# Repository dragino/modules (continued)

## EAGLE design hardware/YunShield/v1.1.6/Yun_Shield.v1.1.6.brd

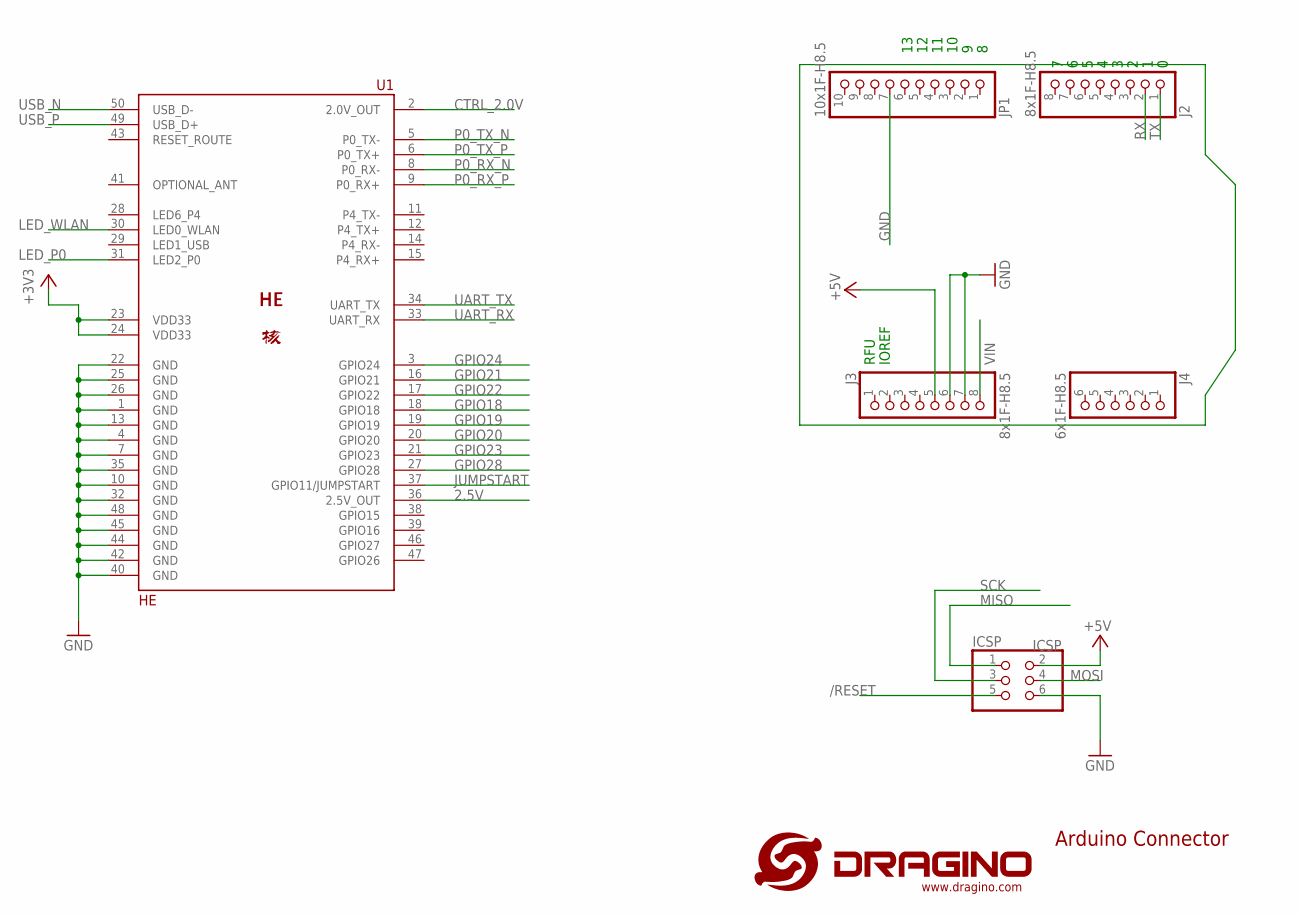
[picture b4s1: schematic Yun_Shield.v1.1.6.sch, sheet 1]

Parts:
ICSP: ICSP; 2X03
J2, J3: 8x1F-H8.5; 1X08
J4: 6x1F-H8.5; 1X06
JP1: 10x1F-H8.5; 1X10
U1: HE; HE50
U$1: LOGO-NEW; LOGO-SILK-NEW

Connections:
2.5V: U1.36 (2.5V_OUT)
5V: ICSP.2
+3V3: U1.23 (VDD33), U1.24 (VDD33); also elsewhere on the board
+5V: J3.5; also elsewhere on the board
/RESET: ICSP.5; also elsewhere on the board
CTRL_2.0V: U1.2 (2.0V_OUT); also elsewhere on the board
GND: ICSP.6, J3.6, J3.7, JP1.7, U1.1 (GND), U1.4 (GND), U1.7 (GND), U1.10 (GND), U1.13 (GND), U1.22 (GND), U1.25 (GND), U1.26 (GND), U1.32 (GND), U1.35 (GND), U1.40 (GND), U1.42 (GND), U1.44 (GND), U1.45 (GND), U1.48 (GND); also elsewhere on the board
GPIO18: U1.18 (GPIO18); also elsewhere on the board
GPIO19: U1.19 (GPIO19); also elsewhere on the board
GPIO20: U1.20 (GPIO20); also elsewhere on the board
GPIO21: U1.16 (GPIO21); also elsewhere on the board
GPIO22: U1.17 (GPIO22); also elsewhere on the board
GPIO23: U1.21 (GPIO23); also elsewhere on the board
GPIO24: U1.3 (GPIO24); also elsewhere on the board
GPIO28: U1.27 (GPIO28); also elsewhere on the board
JUMPSTART: U1.37 (GPIO11/JUMPSTART); also elsewhere on the board
LED_P0: U1.31 (LED2_P0); also elsewhere on the board
LED_WLAN: U1.30 (LED0_WLAN); also elsewhere on the board
MISO: ICSP.1; also elsewhere on the board
MOSI: ICSP.4; also elsewhere on the board
OPTIONAL_ANT: U1.41 (OPTIONAL_ANT)
P0_RX_N: U1.8 (P0_RX-); also elsewhere on the board
P0_RX_P: U1.9 (P0_RX+); also elsewhere on the board
P0_TX_N: U1.5 (P0_TX-); also elsewhere on the board
P0_TX_P: U1.6 (P0_TX+); also elsewhere on the board
RX: J2.2; also elsewhere on the board
SCK: ICSP.3; also elsewhere on the board
TX: J2.1; also elsewhere on the board
UART_RX: U1.33 (UART_RX); also elsewhere on the board
UART_TX: U1.34 (UART_TX); also elsewhere on the board
USB_N: U1.50 (USB_D-); also elsewhere on the board
USB_P: U1.49 (USB_D+); also elsewhere on the board
VIN: J3.8; also elsewhere on the board

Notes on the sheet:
IOREF
RFU
Arduino Connector

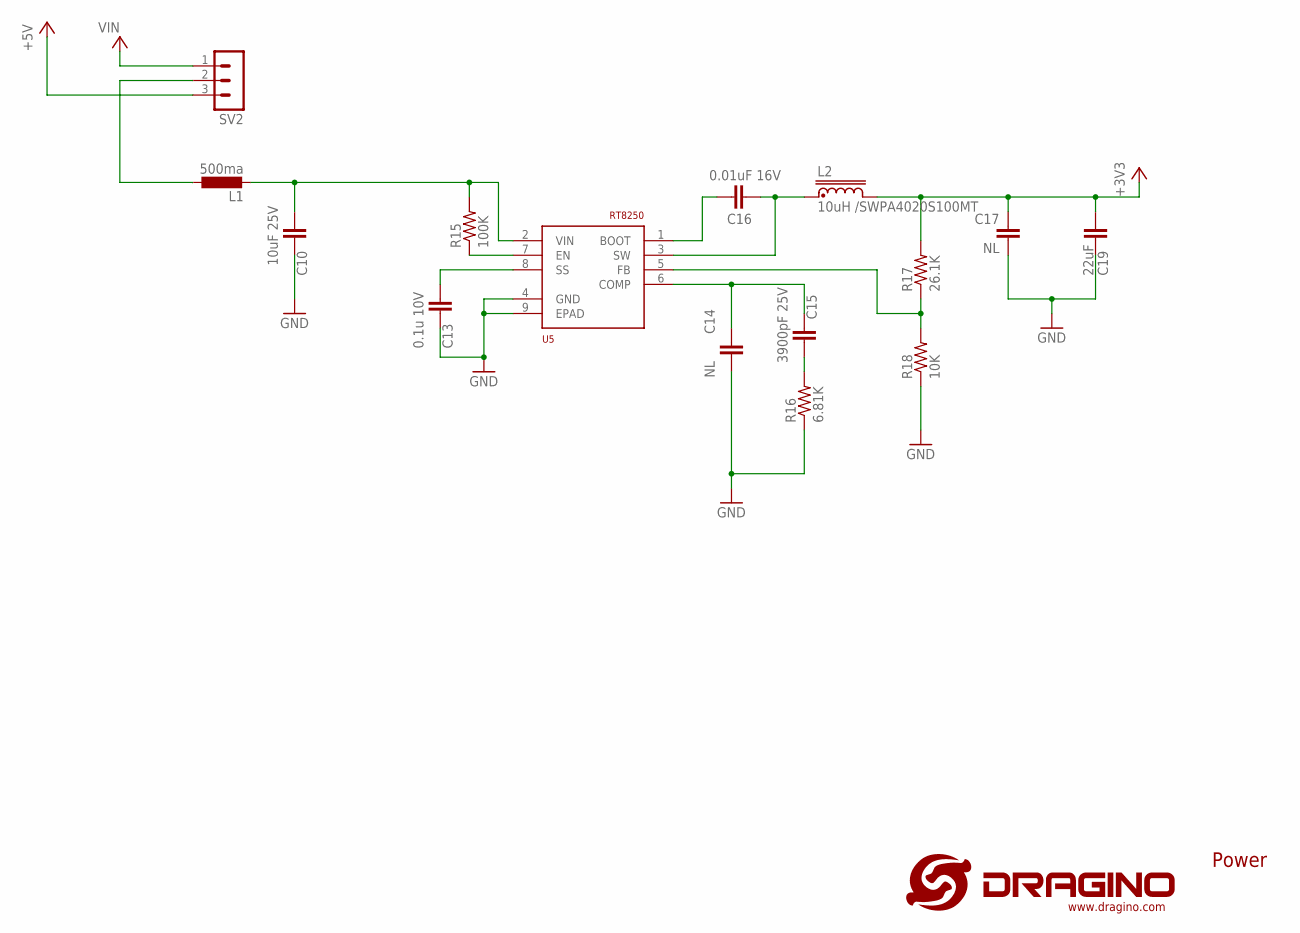
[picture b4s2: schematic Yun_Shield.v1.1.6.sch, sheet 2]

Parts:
C10: 10uF 25V; C1206
C13: 0.1u 10V; C0402
C14, C17: NL; C0402
C15: 3900pF 25V; C0402
C16: 0.01uF 16V; C0402
C19: 22uF; C1210
L1: 500ma; L1812
L2: 10uH /SWPA4020S100MT; SWPA4020S
R15: 100K; R0402
R16: 6.81K; R0402
R17: 26.1K; R0402
R18: 10K; R0402
SV2: MA03-1
U5: RT8250; RT8250-SOP8

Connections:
+3V3: C17.1, C19.1, L2.P$2 (4), R17.2; also elsewhere on the board
+5V: SV2.3; also elsewhere on the board
GND: C10.1, C13.2, C14.2, C17.2, C19.2, R16.1, R18.1, U5.4 (GND), U5.9 (EPAD); also elsewhere on the board
unnamed: C10.2, L1.2, R15.2, U5.2 (VIN)
unnamed: R15.1, U5.7 (EN)
unnamed: R17.1, R18.2, U5.5 (FB)
unnamed: C13.1, U5.8 (SS)
unnamed: C14.1, C15.1, U5.6 (COMP)
unnamed: C15.2, R16.2
unnamed: C16.1, U5.1 (BOOT)
unnamed: C16.2, L2.P$1 (1), U5.3 (SW)
VCC: L1.1, SV2.2
VIN: SV2.1; also elsewhere on the board

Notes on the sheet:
Power

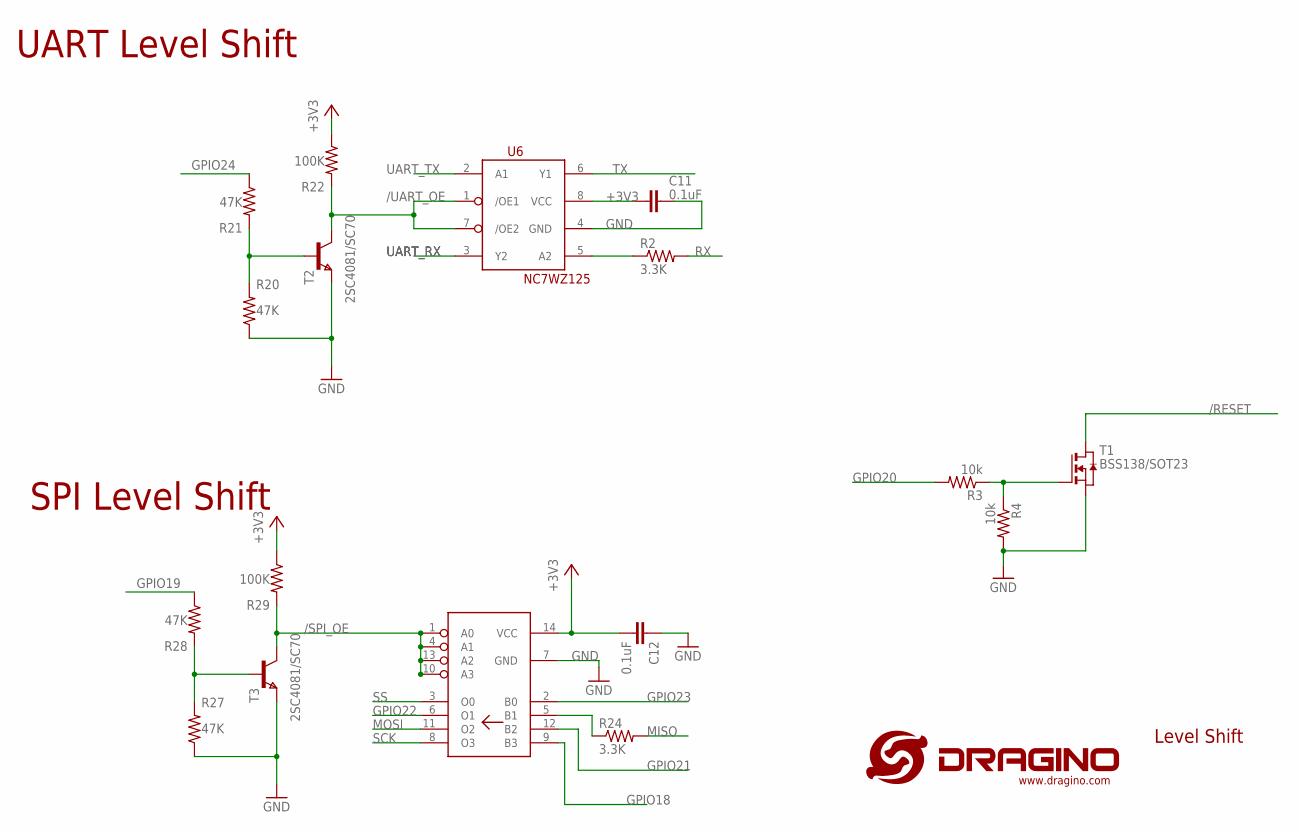
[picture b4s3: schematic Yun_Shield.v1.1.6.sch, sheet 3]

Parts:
C11, C12: 0.1uF; C0402
R2, R24: 3.3K; R0402
R3, R4: 10k; R0402
R20, R21, R27, R28: 47K; R0402
R22, R29: 100K; R0402
T1: BSS138/SOT23; SOT-23
T2, T3: 2SC4081/SC70; SOT323
U6: NC7WZ125; US8
U7: 74VHC125

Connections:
+3V3: C11.2, C12.2, R22.1, R29.1, U6.8 (VCC), U7.14 (VCC); also elsewhere on the board
/RESET: T1.1 (D); also elsewhere on the board
/SPI_OE: R29.2, T3.1 (C), U7.1 (A0), U7.4 (A1), U7.10 (A3), U7.13 (A2)
/UART_OE: R22.2, T2.1 (C), U6.1 (/OE1), U6.7 (/OE2)
GND: C11.1, C12.1, R4.2, R20.1, R27.1, T1.2 (S), T2.3 (E), T3.3 (E), U6.4 (GND), U7.7 (GND); also elsewhere on the board
GPIO18: U7.9 (B3); also elsewhere on the board
GPIO19: R28.1; also elsewhere on the board
GPIO20: R3.2; also elsewhere on the board
GPIO21: U7.12 (B2); also elsewhere on the board
GPIO22: U7.6 (O1); also elsewhere on the board
GPIO23: U7.2 (B0); also elsewhere on the board
GPIO24: R21.1; also elsewhere on the board
MISO: R24.2; also elsewhere on the board
MOSI: U7.11 (O2); also elsewhere on the board
unnamed: R3.1, R4.1, T1.3 (G)
unnamed: R20.2, R21.2, T2.2 (B)
unnamed: R27.2, R28.2, T3.2 (B)
unnamed: R2.1, U6.5 (A2)
unnamed: R24.1, U7.5 (B1)
RX: R2.2; also elsewhere on the board
SCK: U7.8 (O3); also elsewhere on the board
SS: U7.3 (O0)
TX: U6.6 (Y1); also elsewhere on the board
UART_RX: U6.3 (Y2); also elsewhere on the board
UART_TX: U6.2 (A1); also elsewhere on the board

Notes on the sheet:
Level Shift
UART Level Shift
SPI Level Shift

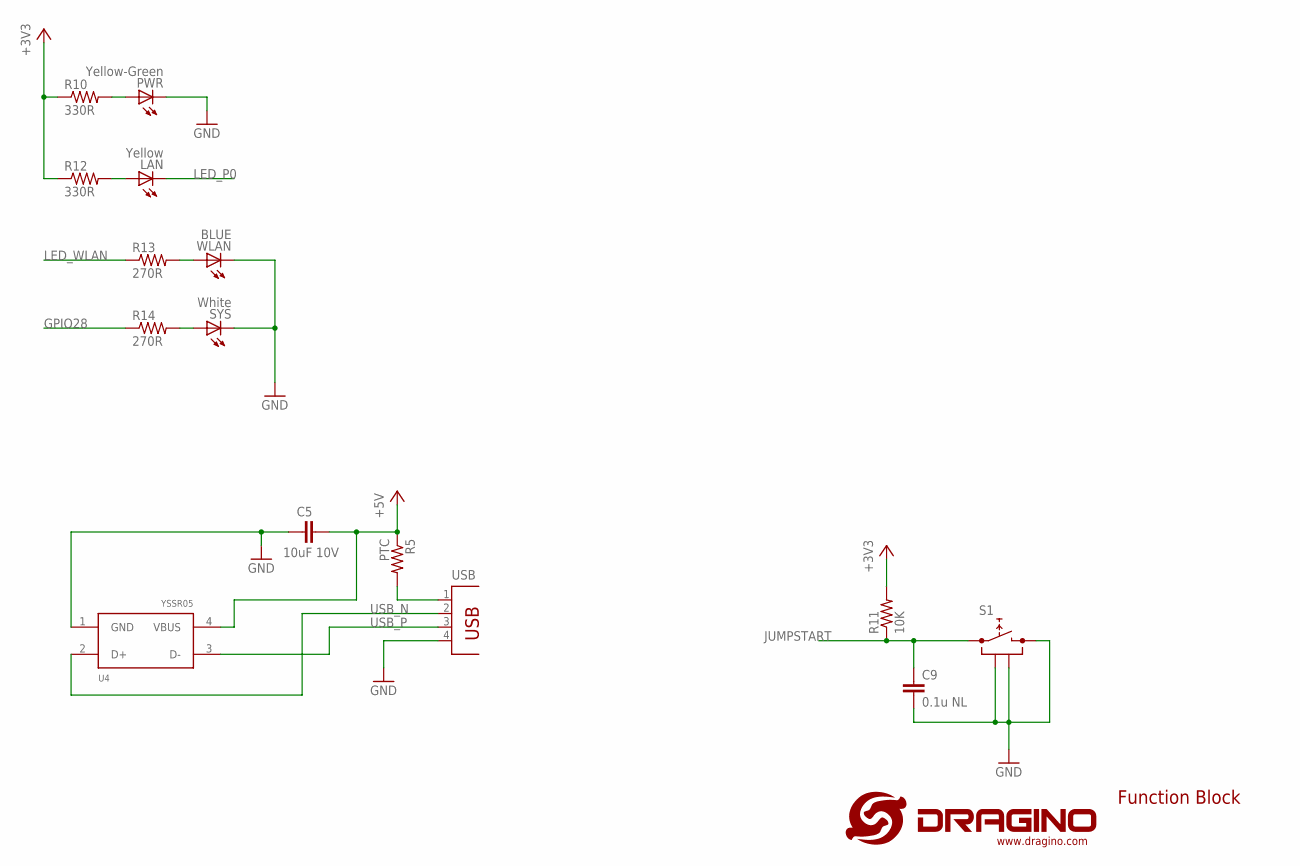
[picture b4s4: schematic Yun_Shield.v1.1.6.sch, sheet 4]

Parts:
C5: 10uF 10V; C0805
C9: 0.1u NL; C0402
LAN: Yellow; CHIP-LED0603
PWR: Yellow-Green; CHIP-LED0603
R5: PTC; R0805
R10, R12: 330R; R0402
R11: 10K; R0402
R13, R14: 270R; R0402
S1: PUSH_SWITCH; SWITCH_6X6X5
SYS: White; CHIP-LED0603
U4: YSSR05; SOT143
USB: PN87520
WLAN: BLUE; CHIP-LED0603

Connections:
+3V3: R10.1, R11.2, R12.1; also elsewhere on the board
+5V: C5.1, R5.1, U4.4 (VBUS); also elsewhere on the board
GND: C5.2, C9.2, PWR.C, S1.2, S1.3, S1.4, SYS.C, U4.1 (GND), USB.4, WLAN.C; also elsewhere on the board
GPIO28: R14.1; also elsewhere on the board
JUMPSTART: C9.1, R11.1, S1.1; also elsewhere on the board
LED_P0: LAN.C; also elsewhere on the board
LED_WLAN: R13.1; also elsewhere on the board
unnamed: R5.2, USB.1
unnamed: PWR.A, R10.2
unnamed: LAN.A, R12.2
unnamed: R13.2, WLAN.A
unnamed: R14.2, SYS.A
USB_N: U4.2 (D+), USB.2; also elsewhere on the board
USB_P: U4.3 (D-), USB.3; also elsewhere on the board

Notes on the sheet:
Function Block

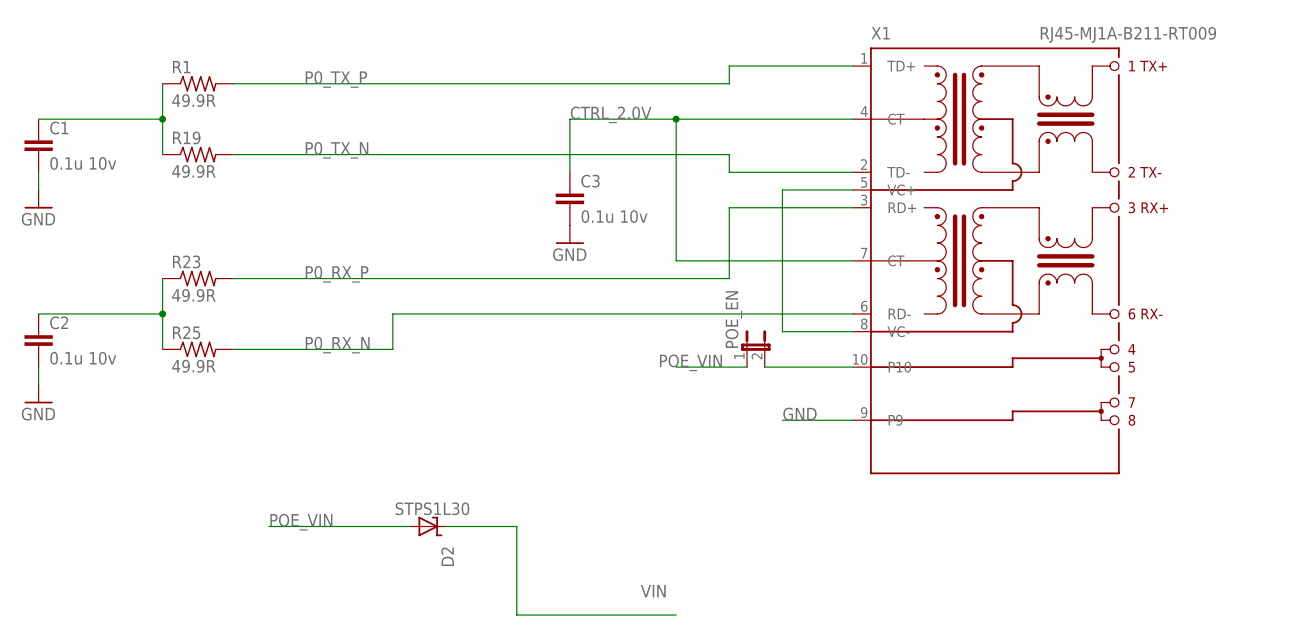
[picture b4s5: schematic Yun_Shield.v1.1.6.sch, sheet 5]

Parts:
C1, C2, C3: 0.1u 10v; C0402
D2: STPS1L30; DO214AC
POE_EN: JP1E; JP1
R1, R19, R23, R25: 49.9R; R0402
X1: RJ45-MJ1A-B211-RT009; MJ1A-B211-RT009

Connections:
CTRL_2.0V: C3.1, X1.4 (CT), X1.7 (CT); also elsewhere on the board
GND: C1.2, C2.2, C3.2, X1.9; also elsewhere on the board
unnamed: POE_EN.2, X1.10
unnamed: X1.5 (VC+), X1.8 (VC-)
unnamed: C1.1, R1.1, R19.1
unnamed: C2.1, R23.1, R25.1
P0_RX_N: R25.2, X1.6 (RD-); also elsewhere on the board
P0_RX_P: R23.2, X1.3 (RD+); also elsewhere on the board
P0_TX_N: R19.2, X1.2 (TD-); also elsewhere on the board
P0_TX_P: R1.2, X1.1 (TD+); also elsewhere on the board
POE_VIN: D2.A, POE_EN.1
VIN: D2.C; also elsewhere on the board

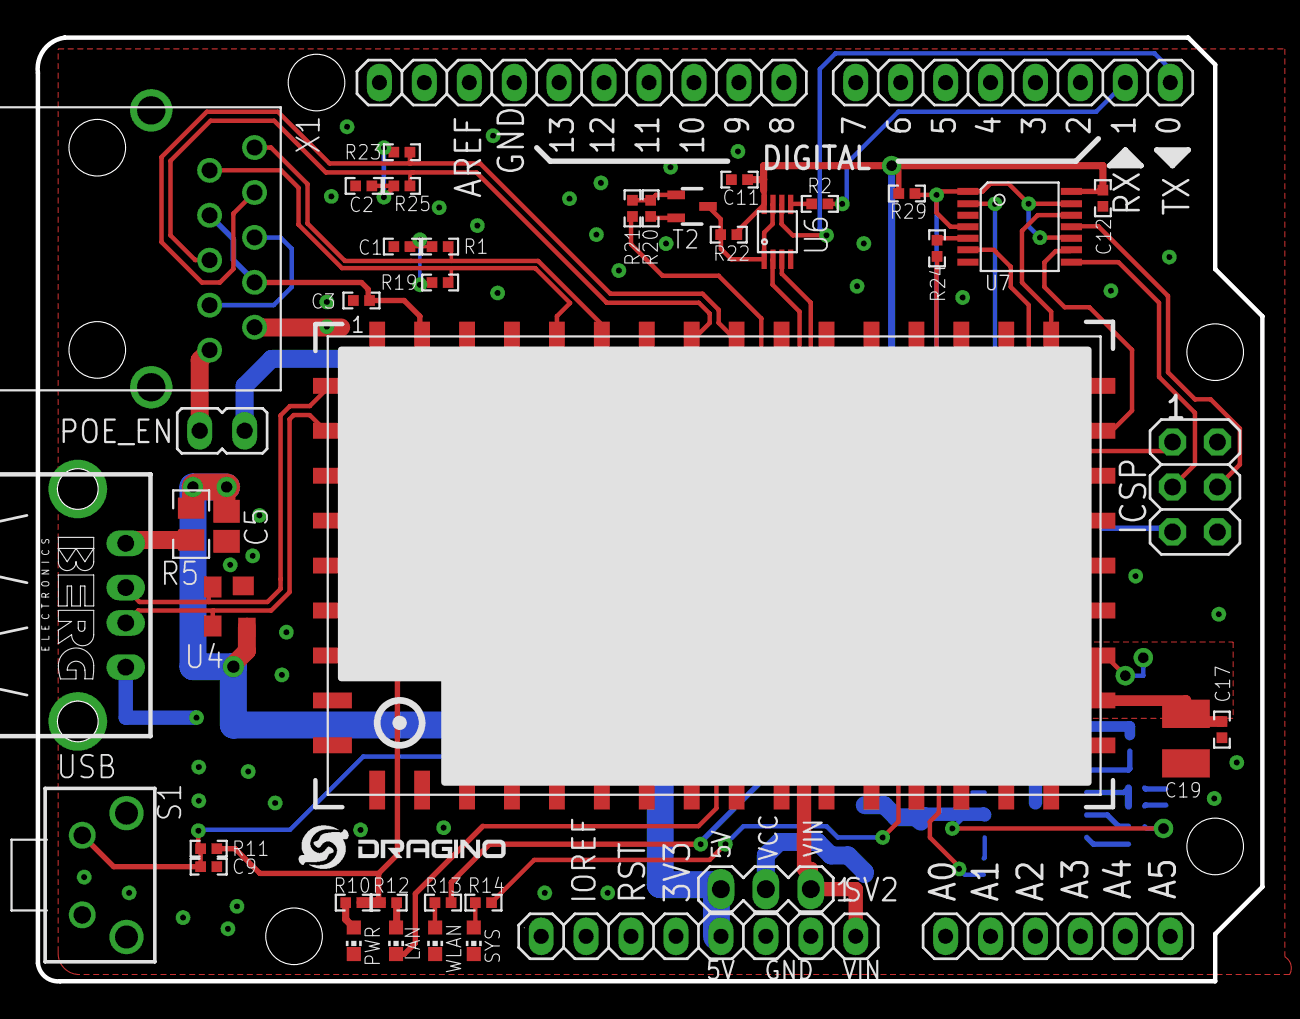
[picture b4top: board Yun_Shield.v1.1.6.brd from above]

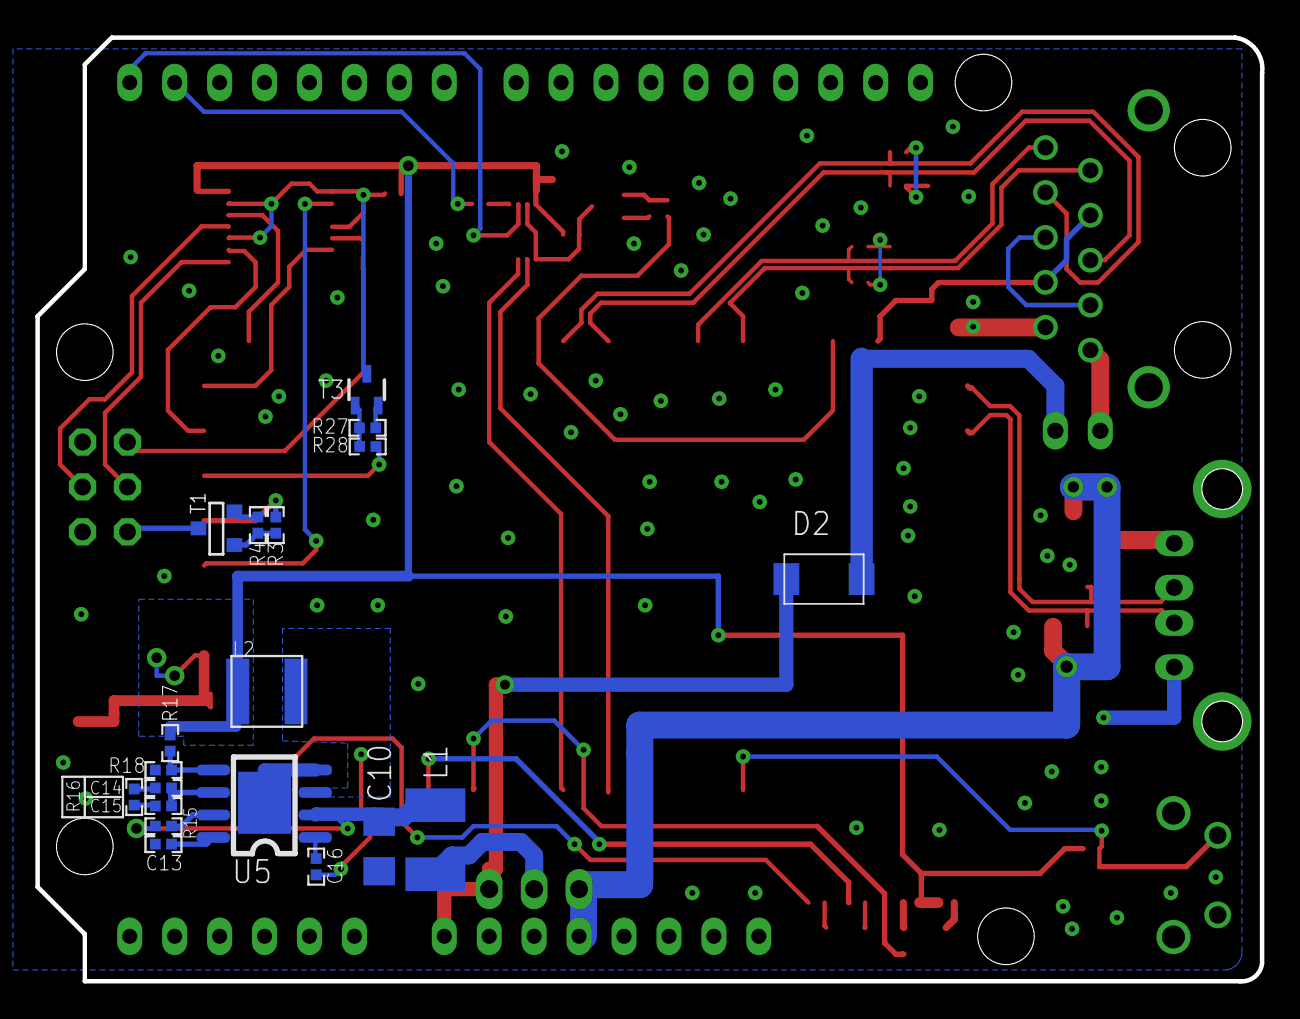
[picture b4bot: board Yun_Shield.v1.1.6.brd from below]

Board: 2 copper layers, 69.2 x 53.3 mm, 64 parts (19 on the bottom side), 56 nets.

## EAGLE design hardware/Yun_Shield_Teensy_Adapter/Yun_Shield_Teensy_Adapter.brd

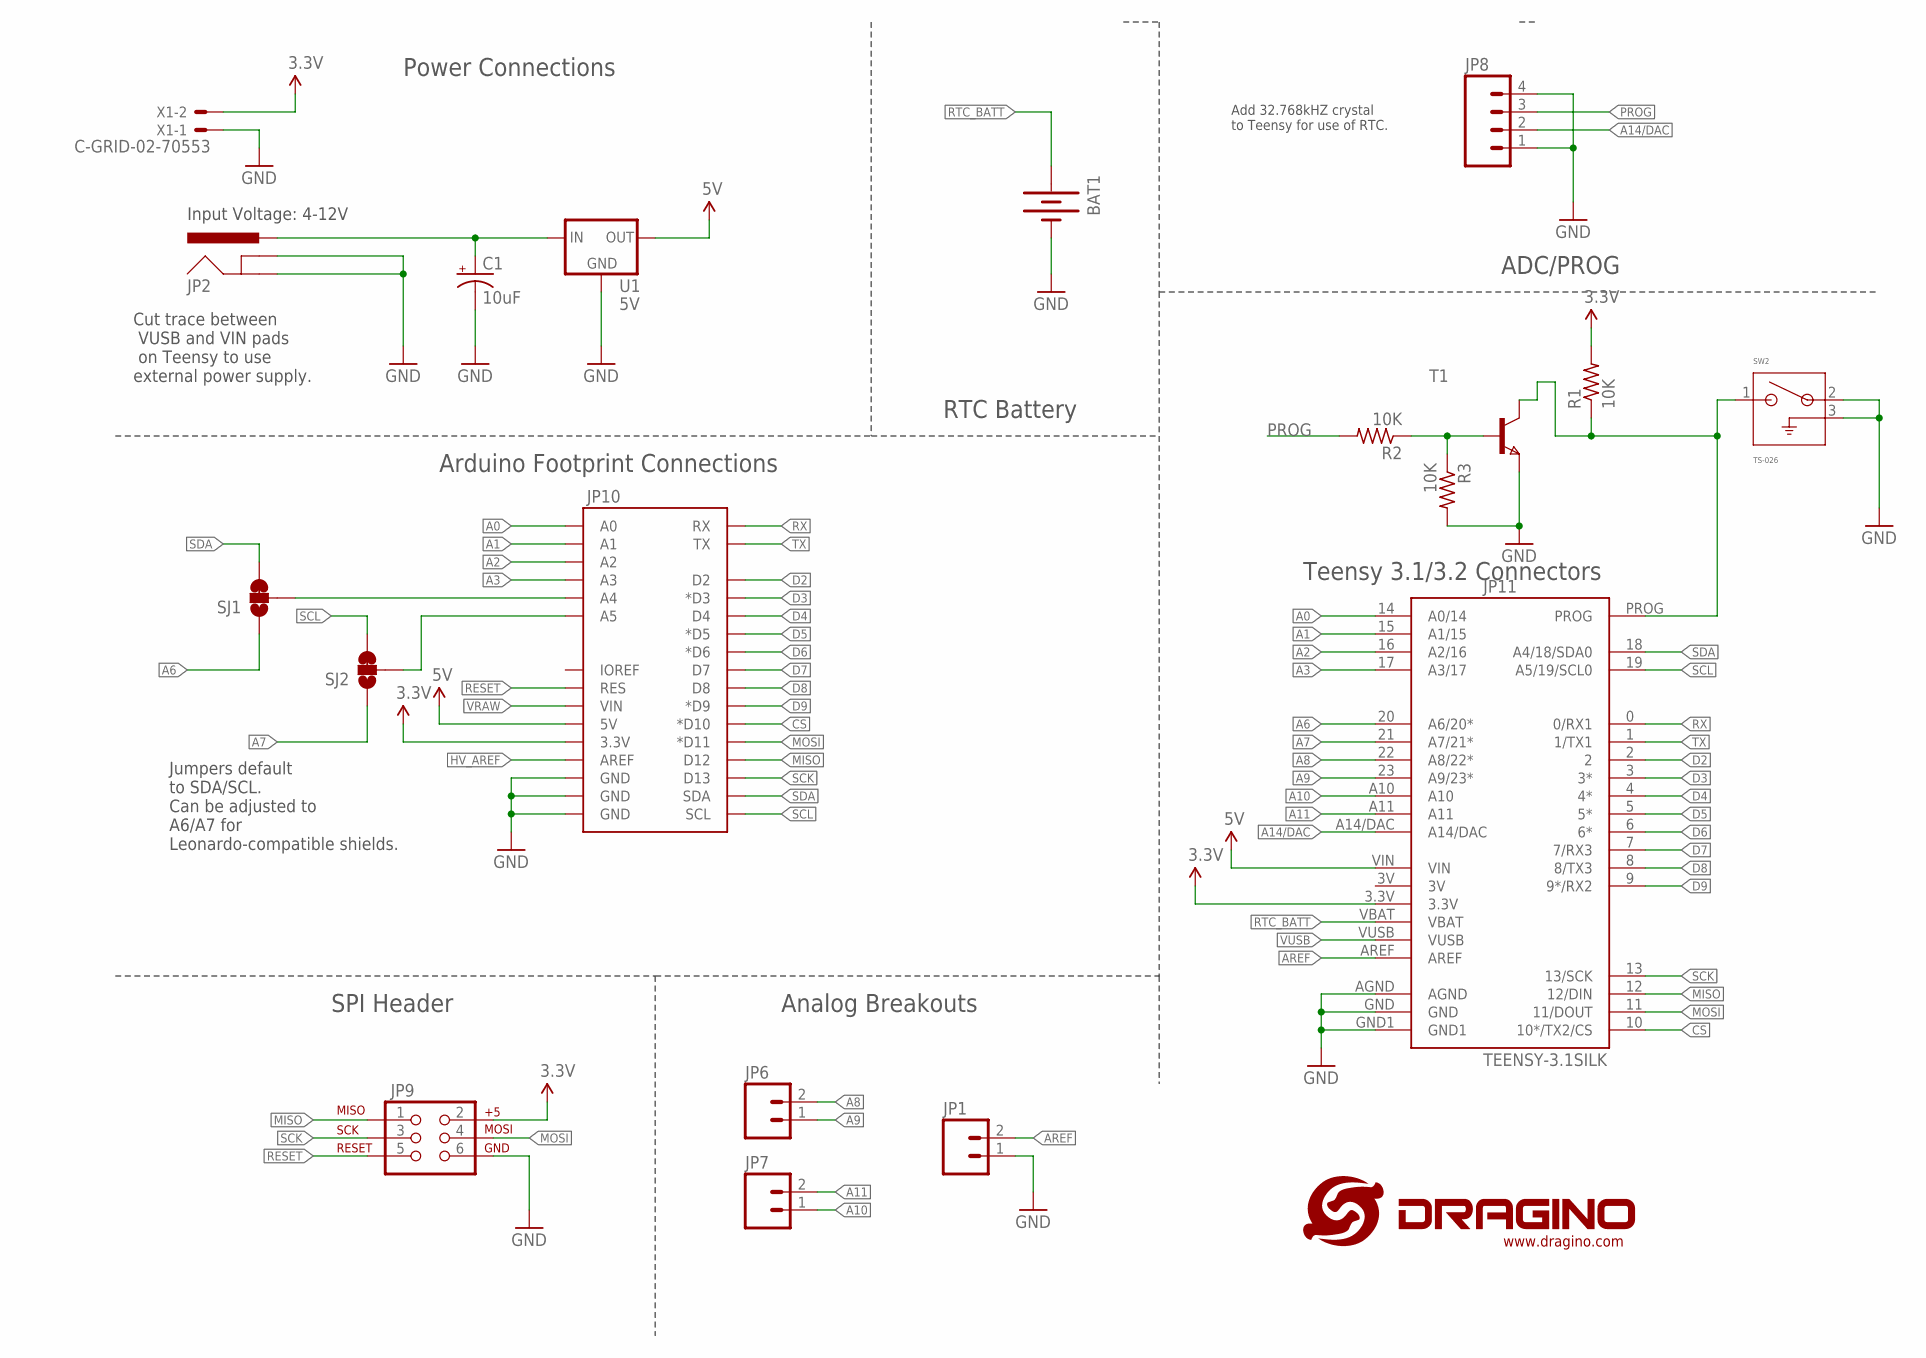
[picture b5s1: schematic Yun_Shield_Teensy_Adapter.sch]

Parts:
BAT1: BATTERY12PTH; BATTCON_12MM_PTH
C1: 10uF; CPOL-RADIAL-10UF-25V
JP1, JP6, JP7: M02PTH; 1X02
JP2: POWER_JACKPTH_LOCK; POWER_JACK_PTH_LOCK
JP8: M04PTH; 1X04
JP9: AVR_SPI_PRG_6PTH; 2X3
JP10: ARDUINO_R3_SHIELDUNO_R3_SHIELD_HOLES; UNO_R3_SHIELD_HOLES
JP11: TEENSY-3.1SILK; TEENSY-3.1
R1, R2, R3: 10K; 0204/5
SJ1, SJ2: JUMPER-PAD-3-2OF3_NC_BY_TRACE_SMALL; PAD-JUMPER-3-2OF3_NC_BY_TRACE_YES_SILK_FULL_BOX
SW2: TS-026
T1: NPN-E3L; E3LINE
U1: 5V; TO-220-ALT
U$1: LOGO-NEW; LOGO-SILK-NEW
X1: C-GRID-02-70553; 70553-02

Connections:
3.3V: JP9.2, JP10.3.3V, JP11.3.3V, R1.2, X1.2
5V: JP10.5V, JP11.VIN, U1.OUT
A0: JP10.A0, JP11.14 (A0/14)
A1: JP10.A1, JP11.15 (A1/15)
A2: JP10.A2, JP11.16 (A2/16)
A3: JP10.A3, JP11.17 (A3/17)
A4: JP10.A4, SJ1.2
A5: JP10.A5, SJ2.2
A6: JP11.20 (A6/20*), SJ1.1
A7: JP11.21 (A7/21*), SJ2.1
A8: JP6.2, JP11.22 (A8/22*)
A9: JP6.1, JP11.23 (A9/23*)
A10: JP7.1, JP11.A10
A11: JP7.2, JP11.A11
A14/DAC: JP8.2, JP11.A14/DAC
AREF: JP1.2, JP11.AREF
CS: JP10.D10 (*D10), JP11.10 (10*/TX2/CS)
D2: JP10.D2, JP11.2
D3: JP10.D3 (*D3), JP11.3 (3*)
D4: JP10.D4, JP11.4 (4*)
D5: JP10.D5 (*D5), JP11.5 (5*)
D6: JP10.D6 (*D6), JP11.6 (6*)
D7: JP10.D7, JP11.7 (7/RX3)
D8: JP10.D8, JP11.8 (8/TX3)
D9: JP10.D9 (*D9), JP11.9 (9*/RX2)
GND: BAT1.GND (-), C1.2 (-), JP1.1, JP2.GND, JP2.GNDBREAK, JP8.1, JP8.4, JP9.6, JP10.GND@0 (GND), JP10.GND@1 (GND), JP10.GND@2 (GND), JP11.AGND, JP11.GND, JP11.GND1, R3.2, SW2.2, SW2.3, T1.3 (E), U1.GND, X1.1
HV_AREF: JP10.AREF
MISO: JP9.1, JP10.D12, JP11.12 (12/DIN)
MOSI: JP9.4, JP10.D11 (*D11), JP11.11 (11/DOUT)
unnamed: JP11.PROG, R1.1, SW2.1, T1.1 (C)
unnamed: R2.1, R3.1, T1.2 (B)
PROG: JP8.3, R2.2
RESET: JP9.5, JP10.RES
RTC_BATT: BAT1.VCC@1 (+), JP11.VBAT
RX: JP10.RX, JP11.0 (0/RX1)
SCK: JP9.3, JP10.D13, JP11.13 (13/SCK)
SCL: JP10.SCL, JP11.19 (A5/19/SCL0), SJ2.3
SDA: JP10.SDA, JP11.18 (A4/18/SDA0), SJ1.3
TX: JP10.TX, JP11.1 (1/TX1)
VRAW: C1.1 (+), JP2.PWR, JP10.VIN, U1.IN
VUSB: JP11.VUSB

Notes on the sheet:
Input Voltage: 4-12V
Add 32.768kHZ crystal to Teensy for use of RTC.
Cut trace between VUSB and VIN pads on Teensy to use external power supply.
Jumpers default to SDA/SCL. Can be adjusted to A6/A7 for Leonardo-compatible shields.
Power Connections
Arduino Footprint Connections
SPI Header
Analog Breakouts
Teensy 3.1/3.2 Connectors
ADC/PROG
RTC Battery

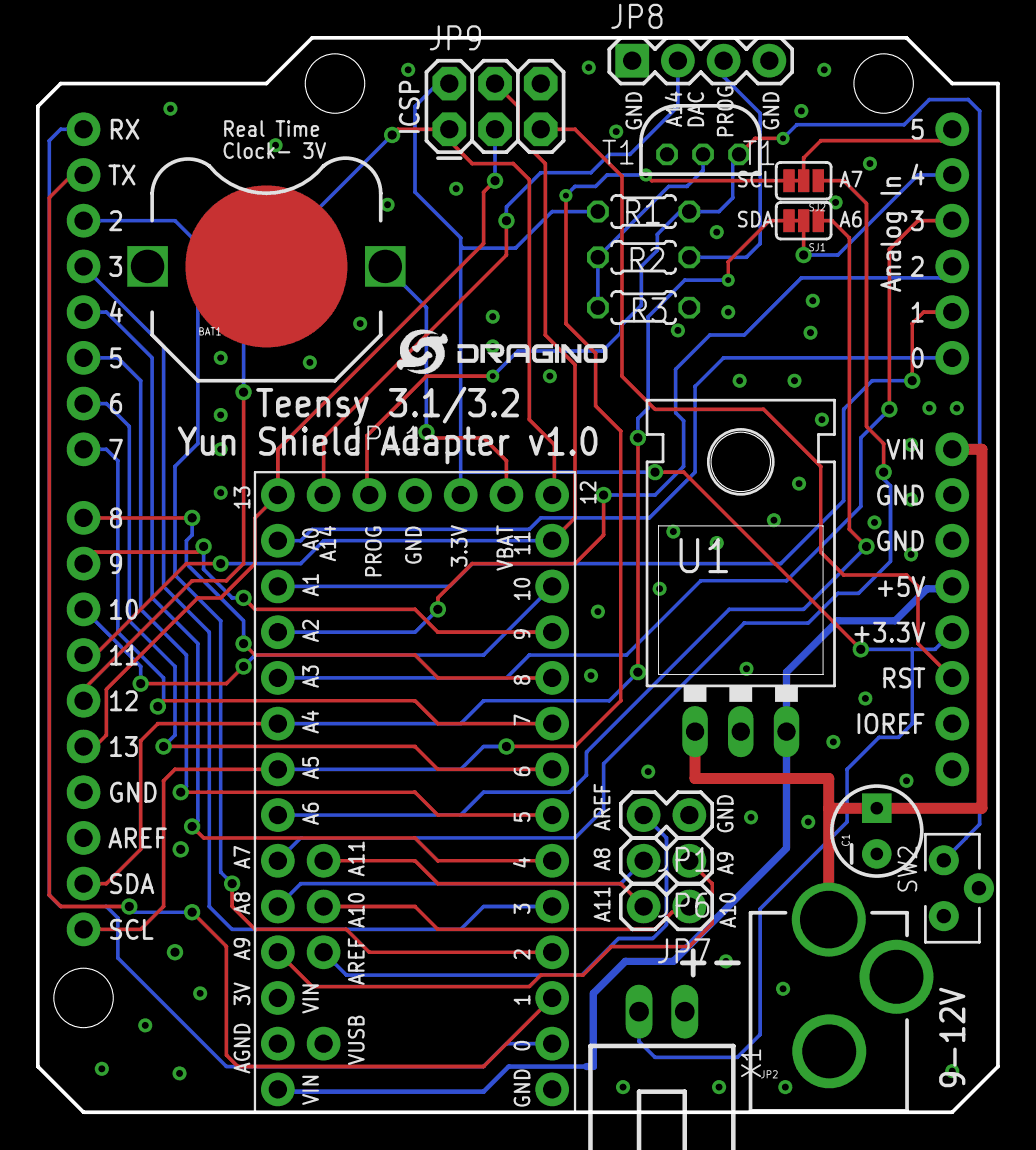
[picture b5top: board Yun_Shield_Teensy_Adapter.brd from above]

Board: 2 copper layers, 53.3 x 59.7 mm, 20 parts (0 on the bottom side), 39 nets.

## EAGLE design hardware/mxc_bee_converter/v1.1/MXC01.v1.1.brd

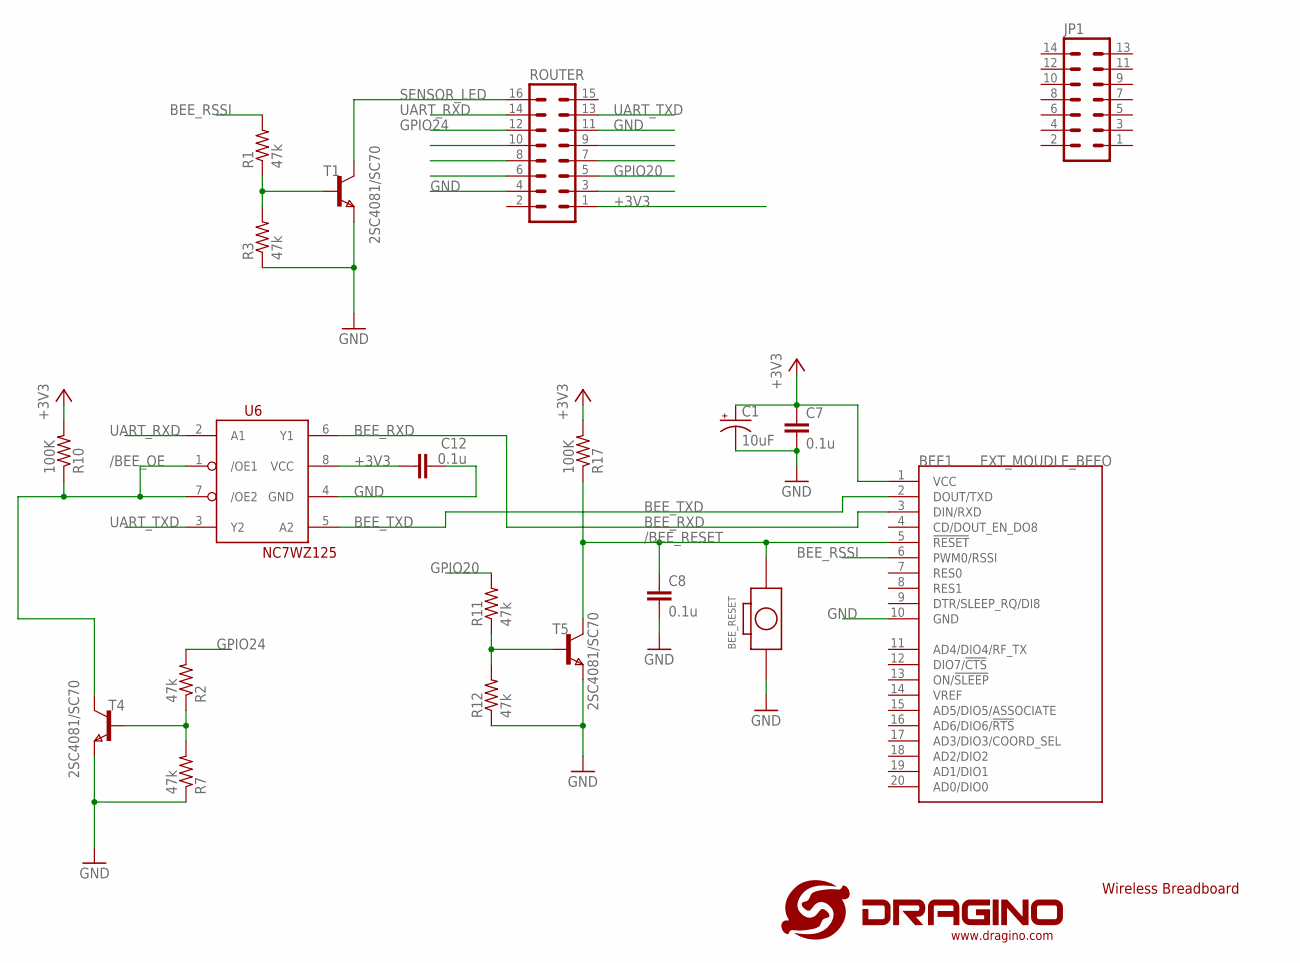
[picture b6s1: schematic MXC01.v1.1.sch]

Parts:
BEE1: EXT_MOUDLE_BEEO; EXT_MOUDLE_BEE
BEE_RESET: CPT_SMD_BOTTON_1_SMD; CPT_SMD_BOTTON_1
C1: 10uF; SMC_A
C7, C8, C12: 0.1u; C0402
JP1: MA07-2
R1, R2, R3, R7, R11, R12: 47k; R0402
R10, R17: 100K; R0402
ROUTER: MA08-2
T1, T4, T5: 2SC4081/SC70; SOT323
U6: NC7WZ125; US8
U$1: LOGO-NEW; LOGO-SILK-NEW

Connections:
+3V3: BEE1.1 (VCC), C1.+, C7.1, C12.1, R10.2, R17.2, ROUTER.1, U6.8 (VCC)
/BEE_OE: R10.1, T4.1 (C), U6.1 (/OE1), U6.7 (/OE2)
/BEE_RESET: BEE1.5 (!RESET), BEE_RESET.P$2 (2), C8.1, R17.1, T5.1 (C)
BEE_RSSI: BEE1.6 (PWM0/RSSI), R1.2
BEE_RXD: BEE1.3 (DIN/RXD), U6.6 (Y1)
BEE_TXD: BEE1.2 (DOUT/TXD), U6.5 (A2)
GND: BEE1.10 (GND), BEE_RESET.1, C1.-, C7.2, C8.2, C12.2, R3.1, R7.1, R12.1, ROUTER.4, ROUTER.11, T1.3 (E), T4.3 (E), T5.3 (E), U6.4 (GND)
GPIO20: R11.2, ROUTER.5
GPIO24: R2.2, ROUTER.12
unnamed: R1.1, R3.2, T1.2 (B)
unnamed: R2.1, R7.2, T4.2 (B)
unnamed: R11.1, R12.2, T5.2 (B)
SENSOR_LED: ROUTER.16, T1.1 (C)
UART_RXD: ROUTER.14, U6.2 (A1)
UART_TXD: ROUTER.13, U6.3 (Y2)

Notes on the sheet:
Wireless Breadboard

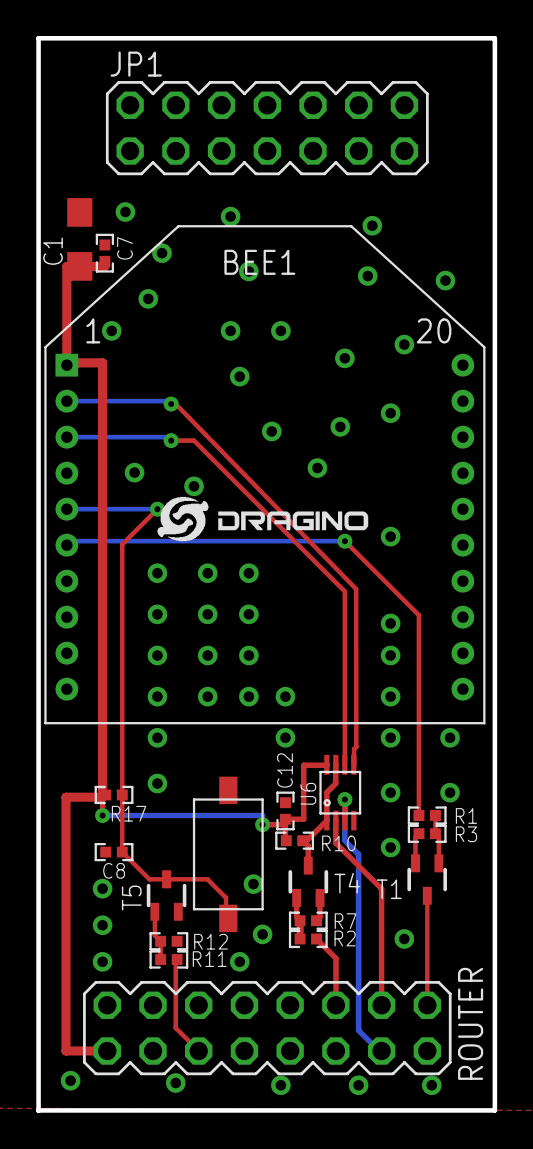
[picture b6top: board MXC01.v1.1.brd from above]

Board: 2 copper layers, 25.4 x 59.6 mm, 21 parts (0 on the bottom side), 15 nets.

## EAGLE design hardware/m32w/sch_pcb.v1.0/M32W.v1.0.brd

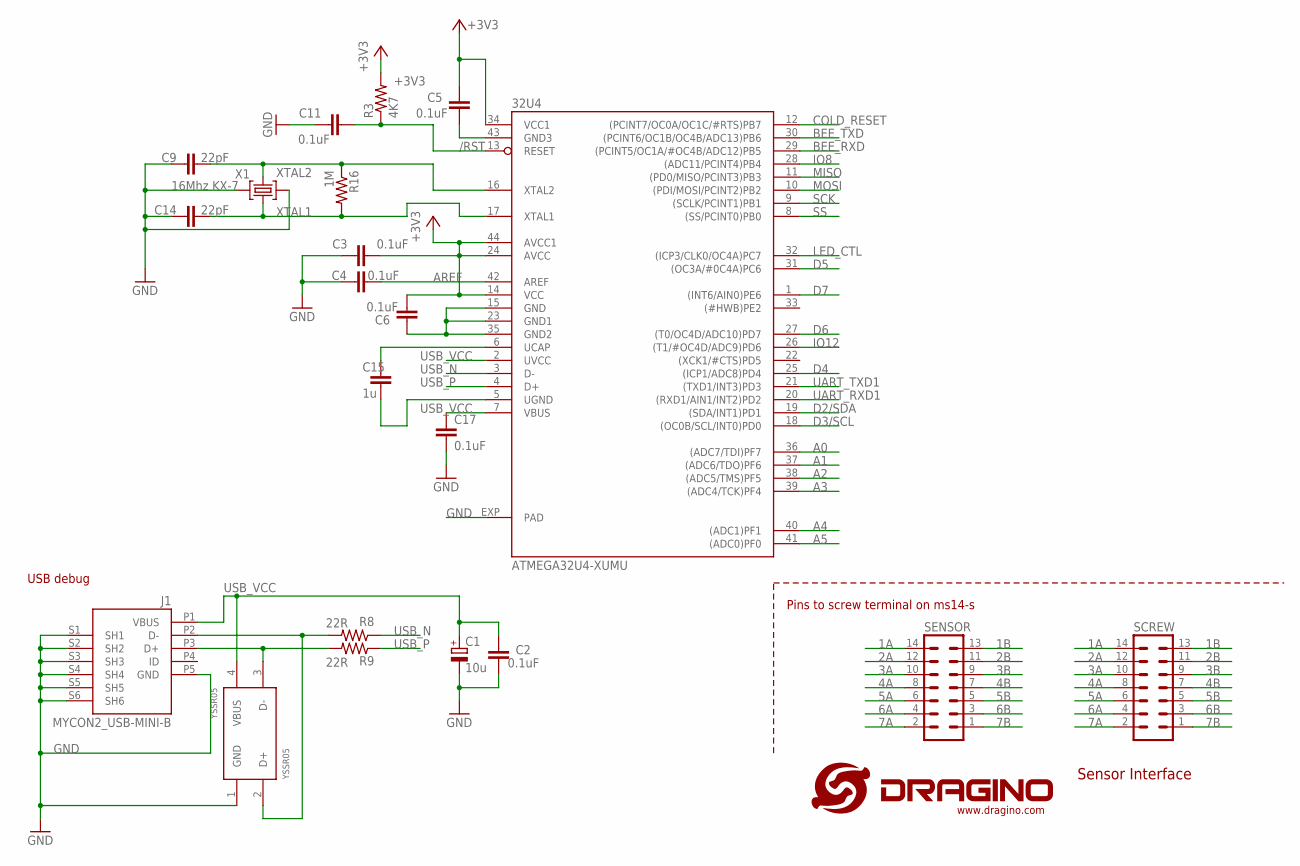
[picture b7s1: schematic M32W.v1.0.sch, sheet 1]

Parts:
32U4: ATMEGA32U4-XUMU; QFN44ML7X7
C1: 10u; SMC_B
C2, C3, C4, C5, C6, C11, C17: 0.1uF; C0402
C9, C14: 22pF; C0402
C15: 1u; C0402
J1: MYCON2_USB-MINI-B; CON2_USB_MICRO_B_AT
R3: 4K7; R0402
R8, R9: 22R; R0402
R16: 1M; R0402
SCREW: MA07-2
SENSOR: MA07-2
X1: 16Mhz KX-7; CRYSTAL-3.2-2.5
YSSR05: YSSR05; SOT143

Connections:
1A: SCREW.14, SENSOR.14
1B: SCREW.13, SENSOR.13
2A: SCREW.12, SENSOR.12
2B: SCREW.11, SENSOR.11
3A: SCREW.10, SENSOR.10
3B: SCREW.9, SENSOR.9
4A: SCREW.8, SENSOR.8
4B: SCREW.7, SENSOR.7
5A: SCREW.6, SENSOR.6
5B: SCREW.5, SENSOR.5
6A: SCREW.4, SENSOR.4
6B: SCREW.3, SENSOR.3
7A: SCREW.2, SENSOR.2
7B: SCREW.1, SENSOR.1
+3V3: 32U4.14 (VCC), 32U4.24 (AVCC), 32U4.34 (VCC1), 32U4.44 (AVCC1), C3.2, C5.1, C6.2, R3.2; also elsewhere on the board
/RST: 32U4.13 (RESET), C11.1, R3.1; also elsewhere on the board
A0: 32U4.36 ((ADC7/TDI)PF7); also elsewhere on the board
A1: 32U4.37 ((ADC6/TDO)PF6); also elsewhere on the board
A2: 32U4.38 ((ADC5/TMS)PF5); also elsewhere on the board
A3: 32U4.39 ((ADC4/TCK)PF4); also elsewhere on the board
A4: 32U4.40 ((ADC1)PF1); also elsewhere on the board
A5: 32U4.41 ((ADC0)PF0); also elsewhere on the board
AREF: 32U4.42 (AREF), C4.2
BEE_RXD: 32U4.29 ((PCINT5/OC1A/#OC4B/ADC12)PB5); also elsewhere on the board
BEE_TXD: 32U4.30 ((PCINT6/OC1B/OC4B/ADC13)PB6); also elsewhere on the board
COLD_RESET: 32U4.12 ((PCINT7/OC0A/OC1C/#RTS)PB7); also elsewhere on the board
D2/SDA: 32U4.19 ((SDA/INT1)PD1); also elsewhere on the board
D3/SCL: 32U4.18 ((OC0B/SCL/INT0)PD0); also elsewhere on the board
D4: 32U4.25 ((ICP1/ADC8)PD4); also elsewhere on the board
D5: 32U4.31 ((OC3A/#0C4A)PC6); also elsewhere on the board
D6: 32U4.27 ((T0/OC4D/ADC10)PD7); also elsewhere on the board
D7: 32U4.1 ((INT6/AIN0)PE6)
GND: 32U4.5 (UGND), 32U4.15 (GND), 32U4.23 (GND1), 32U4.35 (GND2), 32U4.43 (GND3), 32U4.EXP (PAD), C1.-, C2.2, C3.1, C4.1, C5.2, C6.1, C9.1, C11.2, C14.1, C15.1, C17.1, J1.P5 (GND), J1.S1 (SH1), J1.S2 (SH2), J1.S3 (SH3), J1.S4 (SH4), J1.S5 (SH5), J1.S6 (SH6), X1.2 (GND), X1.4 (GND), YSSR05.1 (GND); also elsewhere on the board
IO8: 32U4.28 ((ADC11/PCINT4)PB4); also elsewhere on the board
IO12: 32U4.26 ((T1/#OC4D/ADC9)PD6); also elsewhere on the board
LED_CTL: 32U4.32 ((ICP3/CLK0/OC4A)PC7); also elsewhere on the board
MISO: 32U4.11 ((PD0/MISO/PCINT3)PB3); also elsewhere on the board
MOSI: 32U4.10 ((PDI/MOSI/PCINT2)PB2); also elsewhere on the board
unnamed: 32U4.6 (UCAP), C15.2
unnamed: J1.P3 (D+), R9.2, YSSR05.3 (D-)
unnamed: J1.P2 (D-), R8.2, YSSR05.2 (D+)
SCK: 32U4.9 ((SCLK/PCINT1)PB1); also elsewhere on the board
SS: 32U4.8 ((SS/PCINT0)PB0); also elsewhere on the board
UART_RXD1: 32U4.20 ((RXD1/AIN1/INT2)PD2); also elsewhere on the board
UART_TXD1: 32U4.21 ((TXD1/INT3)PD3); also elsewhere on the board
USB_N: 32U4.3 (D-), R8.1
USB_P: 32U4.4 (D+), R9.1
USB_VCC: 32U4.2 (UVCC), 32U4.7 (VBUS), C1.+, C2.1, C17.2, J1.P1 (VBUS), YSSR05.4 (VBUS)
XTAL1: 32U4.17 (XTAL1), C14.2, R16.2, X1.3 (C2)
XTAL2: 32U4.16 (XTAL2), C9.2, R16.1, X1.1 (C1)

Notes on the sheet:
Sensor Interface
USB debug
Pins to screw terminal on ms14-s
